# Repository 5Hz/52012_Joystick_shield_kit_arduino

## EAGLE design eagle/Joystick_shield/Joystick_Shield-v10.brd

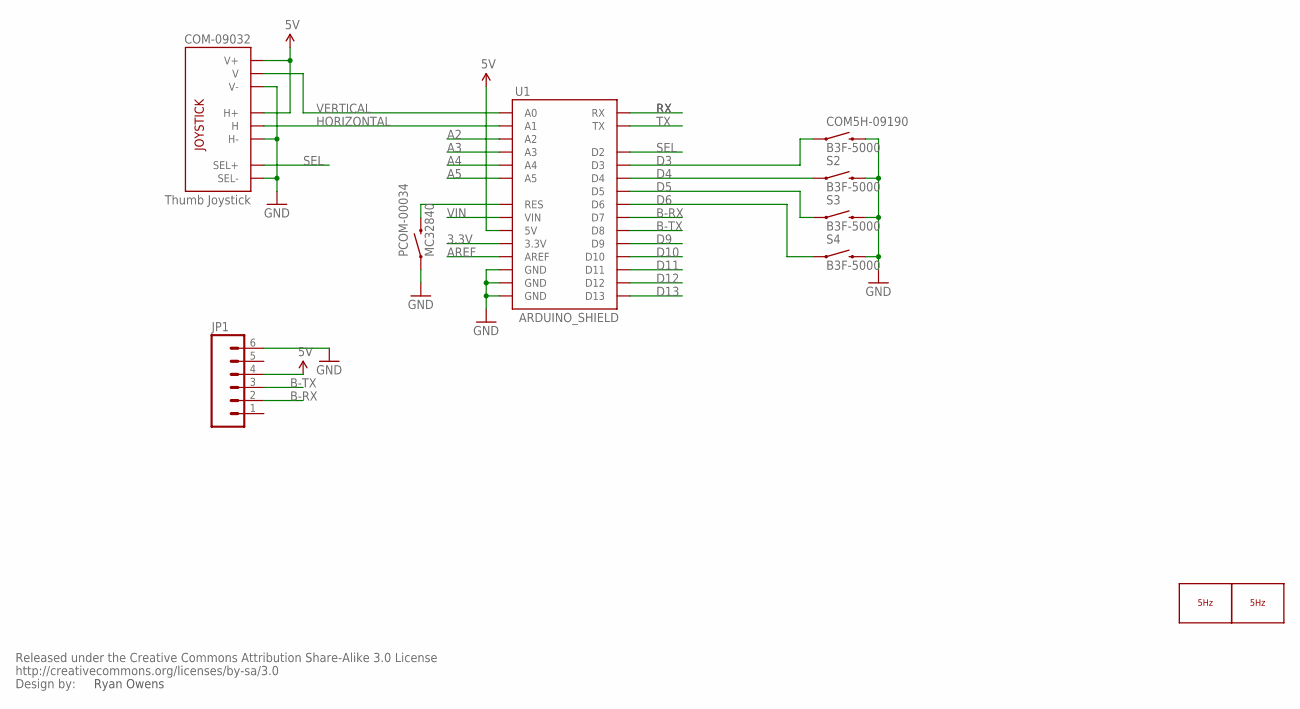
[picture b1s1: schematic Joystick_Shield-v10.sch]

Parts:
COM5H-09190: B3F-5000; TACTILE-PTH-12MM
COM-09032: Thumb Joystick; JOYSTICK
JP1: M06SIP; 1X06
LOGO1: LOGO_5HZ_H_COOPER_15MM; 5HZ_LOGO_H_COOPER_15MM
LOGO2: LOGO_5HZ_MAIN_15MM; 5HZ_LOGO_MAIN_15MM
PCOM-00034: MC32840; TACTILE-PTH
S2, S3, S4: B3F-5000; TACTILE-PTH-12MM
U1: ARDUINO_SHIELD; DUEMILANOVE_SHIELD
U$3: CREATIVE_COMMONS

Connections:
3.3V: U1.3.3V
5V: COM-09032.H1 (H+), COM-09032.V1 (V+), JP1.4, U1.5V
A2: U1.A2
A3: U1.A3
A4: U1.A4
A5: U1.A5
AREF: U1.AREF
B-RX: JP1.2, U1.D7
B-TX: JP1.3, U1.D8
D3: COM5H-09190.1, U1.D3
D4: S2.1, U1.D4
D5: S3.1, U1.D5
D6: S4.1, U1.D6
D9: U1.D9
D10: U1.D10
D11: U1.D11
D12: U1.D12
D13: U1.D13
GND: COM5H-09190.3 (2), COM-09032.B2A (SEL-), COM-09032.H3 (H-), COM-09032.V3 (V-), JP1.6, PCOM-00034.1, S2.3 (2), S3.3 (2), S4.3 (2), U1.GND@0 (GND), U1.GND@1 (GND), U1.GND@2 (GND)
HORIZONTAL: COM-09032.H2 (H), U1.A1
unnamed: PCOM-00034.3 (2), U1.RES
RX: U1.RX
SEL: COM-09032.B1A (SEL+), U1.D2
TX: U1.TX
VERTICAL: COM-09032.V2 (V), U1.A0
VIN: U1.VIN

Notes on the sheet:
Ryan Owens

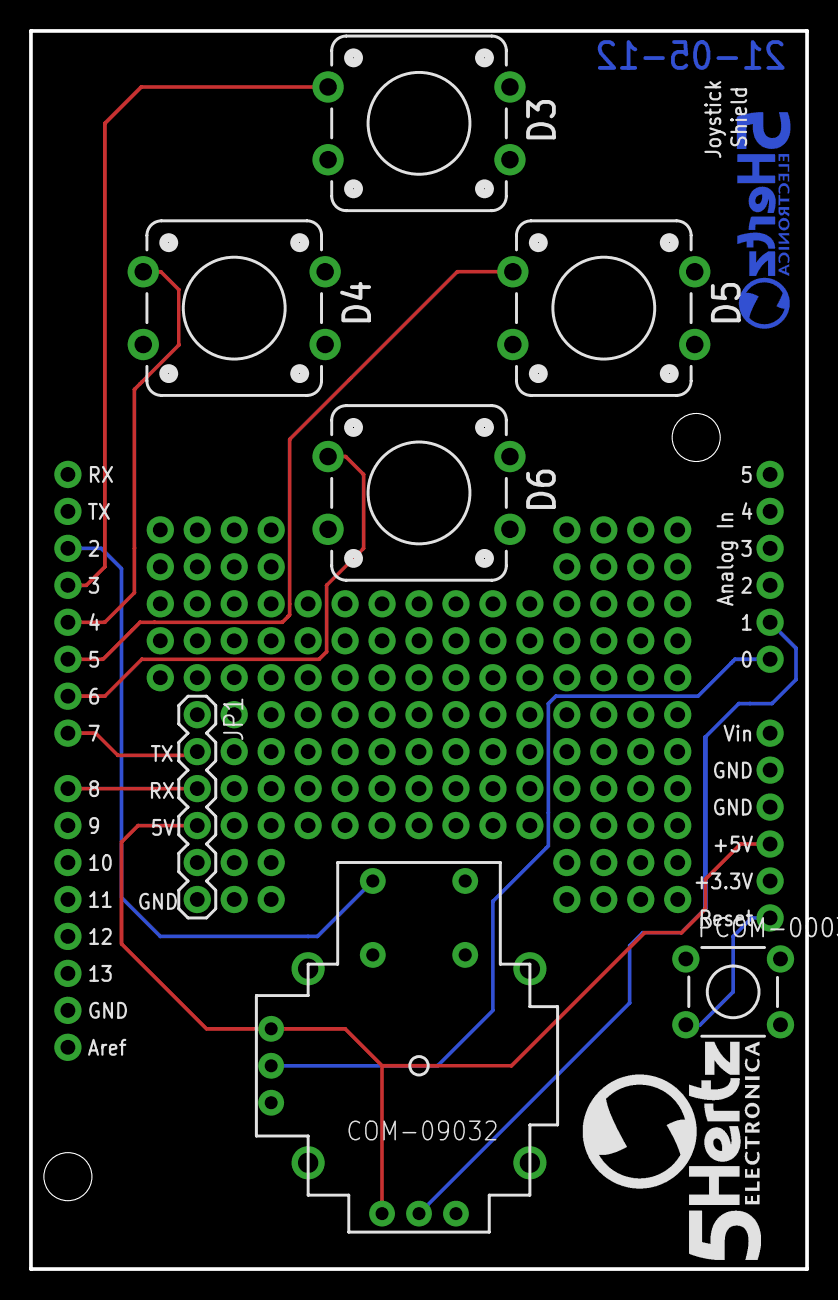
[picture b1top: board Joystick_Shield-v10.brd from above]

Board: 2 copper layers, 53.3 x 85.1 mm, 11 parts (1 on the bottom side), 12 nets.

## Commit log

2014-01-14 creación

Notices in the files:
parts and their libraries:
SparkFun: Released under the Creative Commons Attribution Share-Alike 3.0 License
SparkFun: http://creativecommons.org/licenses/by-sa/3.0
